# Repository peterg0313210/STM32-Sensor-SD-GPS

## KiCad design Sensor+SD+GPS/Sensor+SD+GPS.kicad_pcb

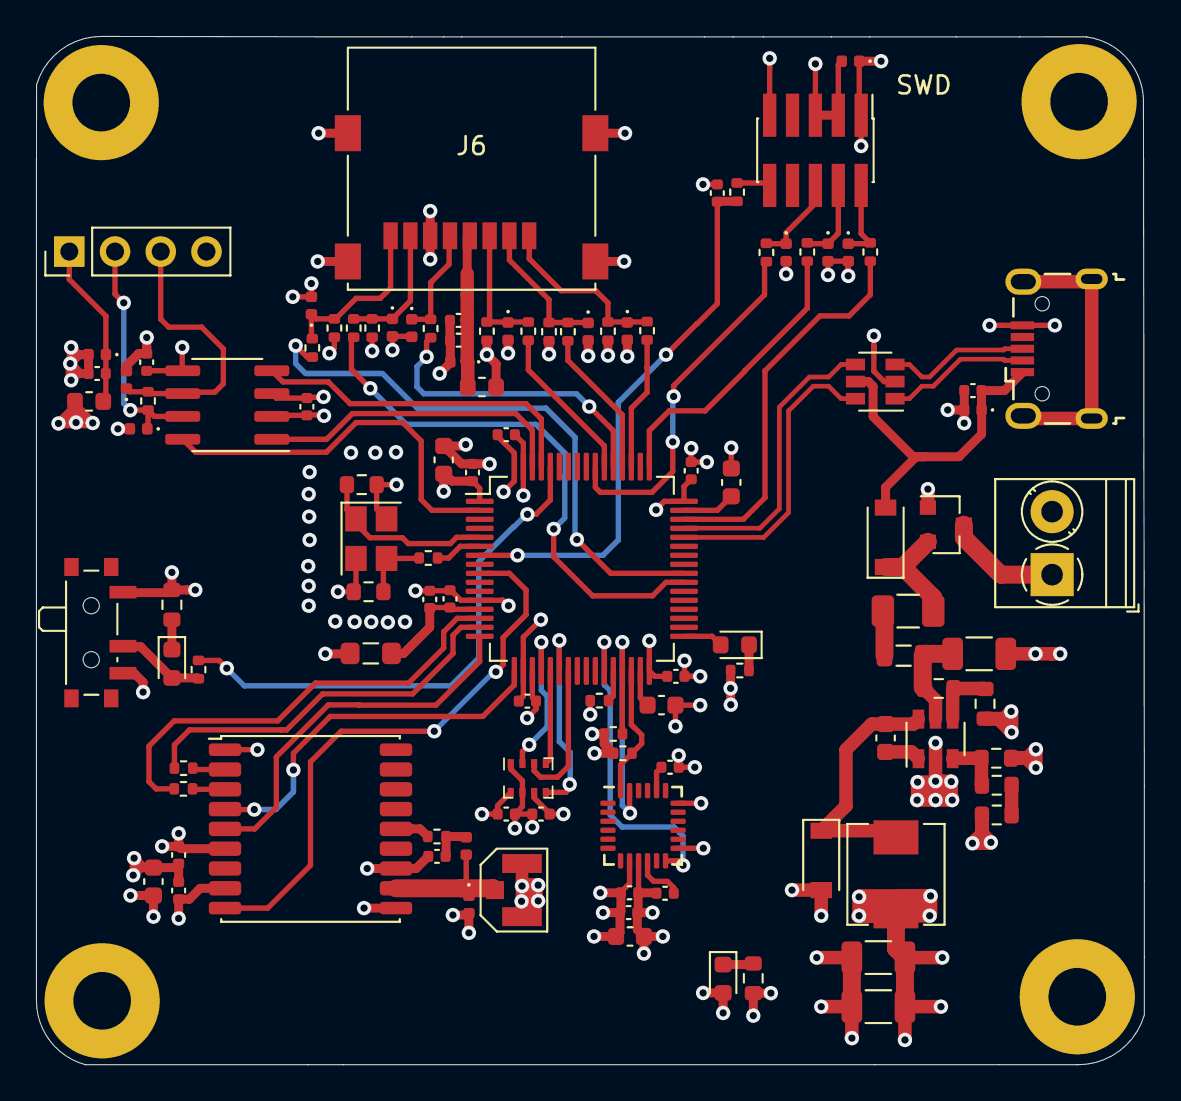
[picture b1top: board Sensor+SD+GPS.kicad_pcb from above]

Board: 4 copper layers, 61.6 x 57.1 mm, 114 parts (0 on the bottom side), 75 nets.

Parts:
C1, C4: 12p; R_0603_1608Metric
C2: 4u7; C_0603_1608Metric
C3, C5, C7, C8, C10, C13, C14, C20, C21, C22, C23, C24, C25, C27, C28, C30, C31, C33, C34: 100n; C_0402_1005Metric
C6, C9: 2u2; C_0603_1608Metric
C11: 1u; C_0402_1005Metric
C12, C29: 10n; C_0402_1005Metric
C15, C17, C18: 10u; C_1206_3216Metric
C16: 10n; C_0603_1608Metric
C19, C26: 10u; C_0603_1608Metric
C32: 10u; C_0402_1005Metric
D1: BLUE; LED_0603_1608Metric
D2, D3, D4, D5, D6, D11, D12, D13, D14, D15, D16, D17, D18, D19, D20: D_TVS; D_0402_1005Metric
D7, D8: B5819W; D_SOD-123
D9: GREEN; LED_0603_1608Metric
D10: RCLAMP0521P-N; D_0402_1005Metric
D21: RED; LED_0603_1608Metric
F1: 250 mA; Fuse_1206_3216Metric
FB1: 600@600MHz; L_0805_2012Metric_Pad1.05x1.20mm_HandSolder
FB2: 600 @ 600MHz; L_0805_2012Metric
FB3, FB4: 100R; L_0603_1608Metric
H1, H2, H3, H4: MountingHole_Pad; MountingHole_3.2mm_M3_Pad
J1: SWD; PinHeader_2x05_P1.27mm_Vertical_SMD
J2: USB_B_Micro; USB_Micro-B_Wuerth_629105150521
J3: 12V Power; TerminalBlock_Phoenix_PT-1,5-2-3.5-H_1x02_P3.50mm_Horizontal
J4: U.FL; BWIPX-1-001E
J5: Conn_01x04; PinHeader_1x04_P2.54mm_Vertical
J6: Micro_SD_Card; TF-102-15
L1: 10u; L_Sunlord_MWSA0518_5.4x5.2mm
L2: 100n; L_0402_1005Metric
Q1: AO3401A; SOT-23
R1: 47; R_0402_1005Metric
R2, R4: 10k; R_0402_1005Metric
R3: 1k; R_0402_1005Metric
R5, R6: 2k2; R_0402_1005Metric
R7, R8, R9, R10: 22R; R_0402_1005Metric
R11: 100k; R_0603_1608Metric
R12: 68k; R_0603_1608Metric
R13: 47k; R_0603_1608Metric
R14: 15k; R_0603_1608Metric
R15: 270; R_0603_1608Metric
R16: 1k5; R_0603_1608Metric
R17, R18, R20, R21, R22, R23, R24, R25: 0R; R_0402_1005Metric
R19: 10R; R_0402_1005Metric
R26: 120R; R_0402_1005Metric
R27, R28, R29, R30, R31: 47k; R_0402_1005Metric
R32: 1k; R_0603_1608Metric
SW1: SW_SPDT; SW_SPDT_PCM12
U1: STM32F405RGTx; LQFP-64_10x10mm_P0.5mm
U2: USBLC6-2SC6; SOT-23-6
U3: MP2359DJ-LF-Z; SOT-23-6
U4: BMP280; Bosch_LGA-8_2x2.5mm_P0.65mm_ClockwisePinNumbering
U5: MPU-6050; InvenSense_QFN-24_4x4mm_P0.5mm
U6: MAX-M8Q; ublox_MAX
U7: TJA1051T-3; SOIC-8_3.9x4.9mm_P1.27mm
Y1: 16MHz; Crystal_SMD_3225-4Pin_3.2x2.5mm

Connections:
+3.3VA: C11.1, C12.1, FB1.1, U1.13
+3V3: C2.1, C3.1, C5.1, C7.1, C8.1, C10.1, C17.2, C18.2, C19.1, C20.1, C21.1, C22.1, C23.1, C26.1, C27.1, C28.1, C30.1, C31.1, D2.1, D9.2, FB1.2, FB3.2, FB4.2, J1.1, L1.2, R5.1, R6.1, R13.1, R27.1, R28.1, R29.1, R30.1, R31.1, SW1.3, U1.1, U1.19, U1.32, U1.48, U1.64, U4.6, U4.8, U5.8, U5.13, U6.6, U6.8, U7.3, U7.5
+5V: C13.2, D6.1, D7.2, J2.1, U2.5
CAN_SILENT: U1.2, U7.8
CONN_USB_D+: J2.3, U2.3
CONN_USB_D-: J2.2, U2.1
GND: C1.2, C2.2, C3.2, C4.2, C5.2, C6.2, C7.2, C8.2, C9.2, C10.2, C11.2, C12.2, C13.1, C14.1, C15.2, C17.1, C18.1, C19.2, C20.2, C21.2, C22.2, C23.2, C24.2, C25.2, C26.2, C27.2, C28.2, C29.2, C30.2, C31.2, C32.2, C33.2, C34.1, D2.2, D3.2, D4.2, D5.2, D6.2, D8.2, D10.2, D11.2, D12.2, D13.2, D14.2, D15.2, D16.2, D17.2, D18.2, D19.2, D20.2, H1.1, H2.1, H3.1, H4.1, J1.3, J1.5, J1.9, J2.5, J3.2, J4.2, J5.4, J6.6, J6.9, Q1.1, R3.2, R4.2, R12.2, R15.2, R16.2, R32.2, SW1.1, U1.12, U1.18, U1.63, U2.2, U3.2, U4.1, U4.7, U5.9, U5.18, U6.1, U6.10, U6.12, U7.2, Y1.2, Y1.4
GPS_NRST: U1.9, U6.9
GPS_ONOFF: U1.16, U6.5
GPS_PPS: U1.17, U6.4
IMU_INTERRUPT: U1.27, U5.12
MCU_CAN1_RX: U1.61, U7.4
MCU_CAN1_TX: U1.62, U7.1
MCU_HSE_IN: C1.1, U1.5, Y1.1
MCU_HSE_OUT: R1.1, U1.6
MCU_I2C2_SCL: R5.2, U1.29, U5.23
MCU_I2C2_SDA: R6.2, U1.30, U5.24
MCU_SDIO_CK: R23.2, U1.53
MCU_SDIO_CMD: R22.2, U1.54
MCU_SDIO_D0: R24.2, U1.39
MCU_SDIO_D1: R25.2, U1.40
MCU_SDIO_D2: R20.2, U1.51
MCU_SDIO_D3: R21.2, U1.52
MCU_SPI1_MISO: U1.22, U4.5
MCU_SPI1_MOSI: U1.23, U4.3
MCU_SPI1_NSS: U1.20, U4.2
MCU_SPI1_SCK: U1.21, U4.4
MCU_SWCLK: R9.1, U1.49
MCU_SWDIO: R8.1, U1.46
MCU_SWO: R10.1, U1.55
MCU_UART4_RX: R18.2, U1.15
MCU_UART4_TX: R17.2, U1.14
MCU_USB_D+: U1.45, U2.4
MCU_USB_D-: U1.44, U2.6
NRST: C14.2, R7.1, U1.7
unnamed: C4.1, R1.2, Y1.3
unnamed: C6.1, U1.31
unnamed: C9.1, U1.47
unnamed: C15.1, FB2.1, R11.1, U3.5
unnamed: C16.1, U3.1
unnamed: C16.2, D8.1, L1.1, U3.6
unnamed: C24.1, U5.10
unnamed: C25.1, U5.20
unnamed: C29.1, L2.1, R19.1
unnamed: C32.1, C33.1, D17.1, FB3.1, J6.4
unnamed: C34.2, D20.1, FB4.1, J5.1
unnamed: D1.1, R3.1
unnamed: D1.2, U1.33
unnamed: D3.1, J1.6, R10.2
unnamed: D4.1, J1.4, R9.2
unnamed: D5.1, J1.2, R8.2
unnamed: D7.1, F1.2, Q1.2
unnamed: D9.1, R16.1
unnamed: D10.1, J4.1, L2.2, U6.11
unnamed: D11.1, J6.1, R20.1, R31.2
unnamed: D12.1, J6.2, R21.1, R30.2
unnamed: D13.1, J6.3, R22.1, R29.2
unnamed: D14.1, J6.5, R23.1
unnamed: D15.1, J6.7, R24.1, R28.2
unnamed: D16.1, J6.8, R25.1, R27.2
unnamed: D18.1, J5.3, R26.2, U7.6
unnamed: D19.1, J5.2, R26.1, U7.7
unnamed: D21.1, R32.1
unnamed: D21.2, R2.2, SW1.2
unnamed: F1.1, FB2.2
unnamed: J1.10, R7.2
unnamed: R2.1, U1.60
unnamed: R4.1, U1.28
unnamed: R11.2, R12.1, U3.4
unnamed: R13.2, R14.1, U3.3
unnamed: R14.2, R15.1
unnamed: R17.1, U6.3
unnamed: R18.1, U6.2
unnamed: R19.2, U6.14
VCC: J3.1, Q1.3
